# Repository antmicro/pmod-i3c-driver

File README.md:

# PMOD I3C Driver

Copyright (c) 2024 [Antmicro](https://www.antmicro.com)

## Overview

This project contains open hardware design files for a simple expansion PCB with two push-pull digital output drivers composed of discrete MOSFETs.
This allows to use the board with FPGA-driven systems to implement I3C output stage driver which can act as open drain or push-pull. 
The driver topology is switchable via digital control signals from FPGA-side.
A separate set of control signals allows to activate pull-up or pull-down resistors connected to the output signals.
The design files were prepared in KiCad 9.x.

## Key features

* Two independent digital output stages configurable as push-pull or open drain
* Switchable pull-up and pull-down resistors
* The board is compatible with PMOD (3.3V logic) expansion connector 
* The board is compatible with a 24-pin proto header (J3) available on AMD (Xilinx) [ZCU106 Evaluation Kit](https://www.xilinx.com/products/boards-and-kits/zcu106.html) 

## Project structure

The main directory contains KiCad PCB project files, a LICENSE, and a README.
The remaining files are stored in the following directories: 

* `img` - contains graphics for this README 
* `doc` - contains board schematic in PDF format

## Licensing

This project is published under the [Apache-2.0](LICENSE) license.

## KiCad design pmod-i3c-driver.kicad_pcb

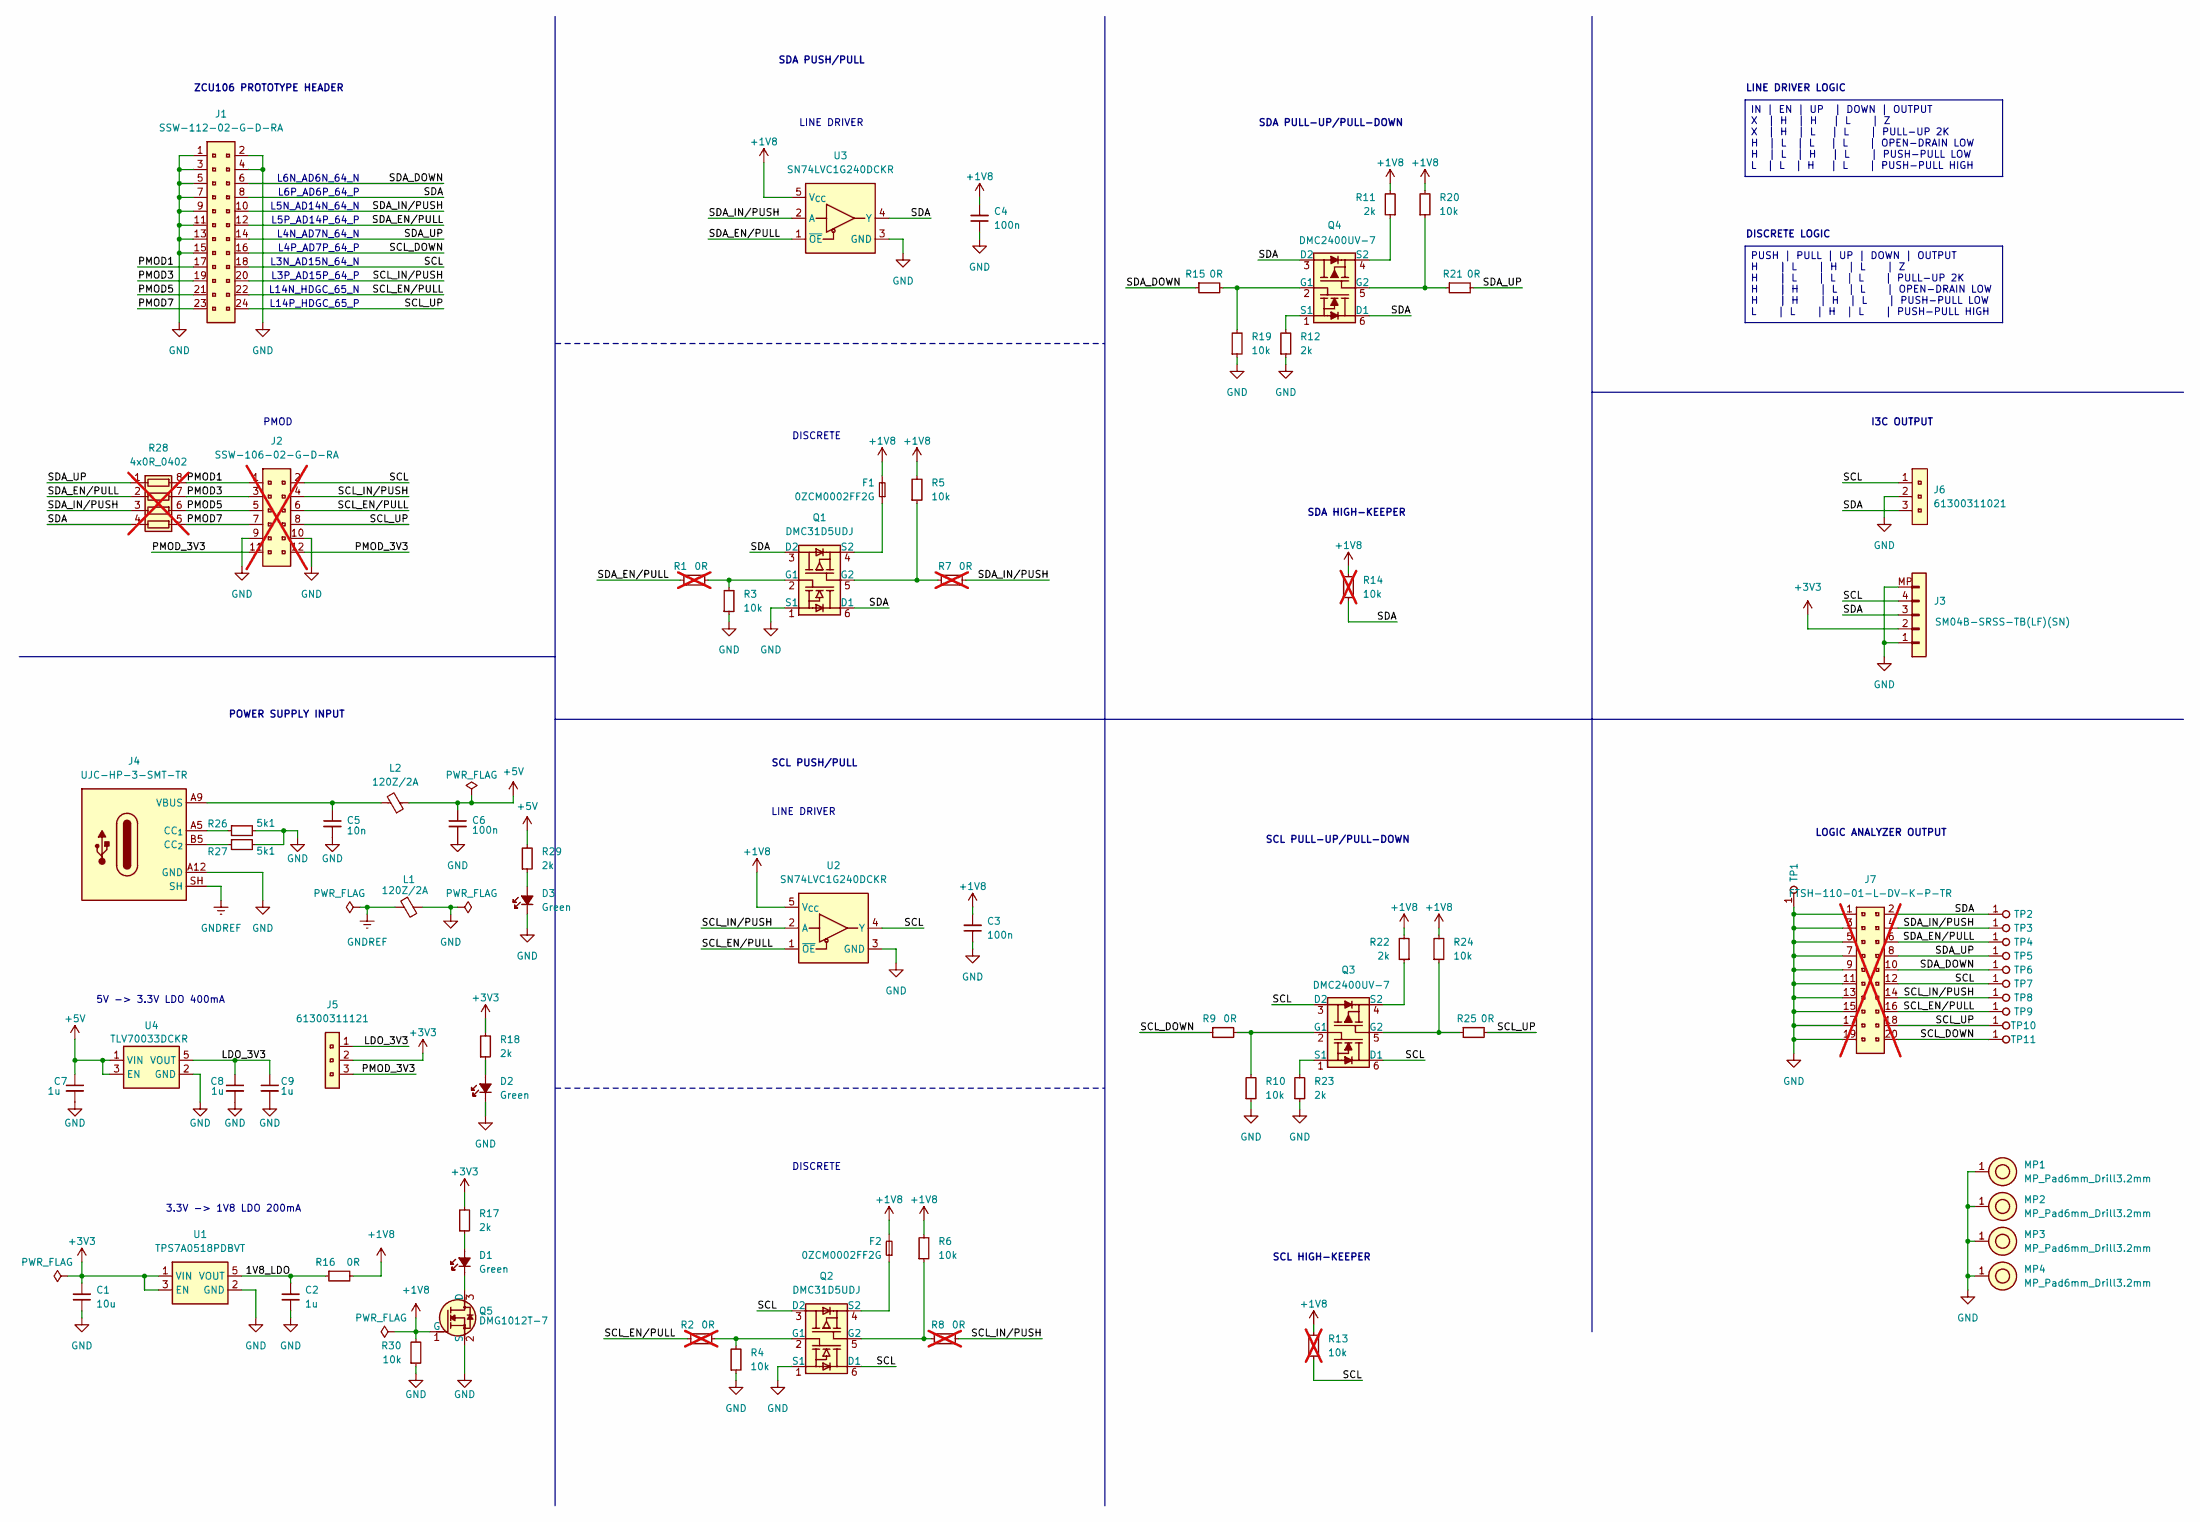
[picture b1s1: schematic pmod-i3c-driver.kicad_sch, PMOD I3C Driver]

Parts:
C1: C_10u_0402; C_0402_1005Metric; MPN CC0402MRX5R5BB106
C2: C_1u_0402; C_0402_1005Metric; MPN C1005X6S1A105K050BC
C3, C4: C_100n_0402; C_0402_1005Metric; Voltage 50V; MPN GRM155R61H104KE14D
C5: C_10n_0402; C_0402_1005Metric; Voltage 50V; MPN GRM155R71H103KA88D
C6: C_100n_16V_X7R_0402; C_0402_1005Metric; Voltage 16V; MPN C0402C104J4RAC7411
C7, C8, C9: C_1u_0603; C_0603_1608Metric; MPN 0603YD105KAT2A
D1, D2, D3: LED_G_0402_VLMTG1500-GS08; LED_0402_1005Metric_G; MPN VLMTG1500-GS08
F1, F2: F_20mA_0603; F_0603_1608Metric; MPN 0ZCM0002FF2G
J1: PinSocket_2x12_P2.54mm_Drill1.04mm_Horizontal; MPN SSW-112-02-G-D-RA
J2: PinSocket_2x6_P2.54mm_Drill1.04mm_Horizontal; MPN SSW-106-02-G-D-RA; not fitted
J3: JST_SH_1x4_SM04B-SRSS-TB-LF-SN; Conn_JST_SH_1x4_SM04B-SRSS-TB-LF-SN; MPN SM04B-SRSS-TB(LF)(SN)
J4: USB-C_CUI_UJC-HP-3-SMT-TR; USB-C_Receptacle_CUI_UJC-HP-3-SMT-TR; MPN UJC-HP-3-SMT-TR
J5: PinHeader_1x3_P2.54mm_Drill1.1mm; MPN 61300311121
J6: PinHeader_1x3_P2.54mm_Drill1.1mm_Horizontal; PinHeader_1x3_P2.54mm_Horizontal; MPN 61300311021
J7: PinHeader_2x10_P1.27mm_SMD_Latch; MPN FTSH-110-01-L-DV-K-P-TR; not fitted
L1, L2: FB_120Z_2A_Murata-BLM18PG_0603; FB_0603_1608Metric; MPN BLM18PG121SN1D
MP1, MP2, MP3, MP4: MP_Pad6mm_Drill3.2mm
Q1, Q2: DMC31D5UDJ; SOT-963; MPN DMC31D5UDJ
Q3, Q4: DMC2400UV-7; SOT-563; MPN DMC2400UV-7
Q5: DMG1012T-7; SOT-523; MPN DMG1012T-7
R1, R2, R7, R8: R_0R_0402; R_0402_1005Metric; MPN ERJ2GE0R00X; not fitted
R3, R4, R5, R6, R10, R19, R20, R24, R30: R_10k_0402; R_0402_1005Metric; Tolerance 1%; MPN CR0402-FX-1002GLF
R9, R15, R16, R21, R25: R_0R_0402; R_0402_1005Metric; MPN ERJ2GE0R00X
R11, R12, R17, R18, R22, R23, R29: R_2k_0402; R_0402_1005Metric; Tolerance 1%; MPN CR0402-FX-2001GLF
R13, R14: R_10k_0402; R_0402_1005Metric; Tolerance 1%; MPN CR0402-FX-1002GLF; not fitted
R26, R27: R_5k1_0402; R_0402_1005Metric; Tolerance 1%; MPN CR0402-FX-5101GLF
R28: 4x0R_0402_array; 4x0R_0402_array_EXB28V; MPN EXB28VR000X; not fitted
TP1, TP2, TP3, TP4, TP5, TP6, TP7, TP8, TP9, TP10, TP11: TP_1.5mm_SMD; TP_SMD_1.5mm
U1: TPS7A0518P_SOT23-5; SOT-23-5; MPN TPS7A0518PDBVT
U2, U3: SN74LVC1G240_SC70; SOT-353; MPN SN74LVC1G240DCKR
U4: TLV70033_SC70; SC-70-5; MPN TLV70033DCKR

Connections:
+1V8: C3.2, C4.2, F1.2, F2.2, Q5.1 (G), R5.2, R6.2, R11.2, R13.2, R14.2, R16.2, R20.2, R22.2, R24.2, R30.2, U2.5 (V_{CC}), U3.5 (V_{CC})
+3V3: C1.2, J3.2, J5.2, R17.2, R18.2, U1.1 (VIN), U1.3 (EN)
+5V: C6.1, C7.1, L2.1, R29.2, U4.1 (VIN), U4.3 (EN)
/1V8_LDO: C2.2, R16.1, U1.5 (VOUT)
/LDO_3V3: C8.1, C9.1, J5.1, U4.5 (VOUT)
/PMOD1: J1.17, J2.1, R28.8 (R1.2)
/PMOD3: J1.19, J2.3, R28.7 (R2.2)
/PMOD5: J1.21, J2.5, R28.6 (R3.2)
/PMOD7: J1.23, J2.7, R28.5 (R4.2)
/PMOD_3V3: J2.11, J2.12, J5.3
/SCL: J1.18, J2.2, J3.4, J6.1, J7.12, Q2.3 (D2), Q2.6 (D1), Q3.3 (D2), Q3.6 (D1), R13.1, TP7.1, U2.4 (Y)
/SCL_DOWN: J1.16, J7.20, R9.1, TP11.1
/SCL_EN/PULL: J1.22, J2.6, J7.16, R2.1, TP9.1, U2.1 (~OE)
/SCL_IN/PUSH: J1.20, J2.4, J7.14, R8.2, TP8.1, U2.2 (A)
/SCL_UP: J1.24, J2.8, J7.18, R25.2, TP10.1
/SDA: J1.8, J3.3, J6.3, J7.2, Q1.3 (D2), Q1.6 (D1), Q4.3 (D2), Q4.6 (D1), R14.1, R28.4 (R4.1), TP2.1, U3.4 (Y)
/SDA_DOWN: J1.6, J7.10, R15.1, TP6.1
/SDA_EN/PULL: J1.12, J7.6, R1.1, R28.2 (R2.1), TP4.1, U3.1 (~OE)
/SDA_IN/PUSH: J1.10, J7.4, R7.2, R28.3 (R3.1), TP3.1, U3.2 (A)
/SDA_UP: J1.14, J7.8, R21.2, R28.1 (R1.1), TP5.1
GND: C1.1, C2.1, C3.1, C4.1, C5.2, C6.2, C7.2, C8.2, C9.2, D2.1 (C), D3.1 (C), J1.1, J1.2, J1.3, J1.4, J1.5, J1.7, J1.9, J1.11, J1.13, J1.15, J2.9, J2.10, J3.1, J3.MP, J4.A12 (GND), J4.B12 (GND), J6.2, J7.1, J7.3, J7.5, J7.7, J7.9, J7.11, J7.13, J7.15, J7.17, J7.19, L1.2, MP1.1, MP2.1, MP3.1, MP4.1, Q1.1 (S1), Q2.1 (S1), Q5.2 (S), R3.1, R4.1, R10.1, R12.1, R19.1, R23.1, R26.2, R27.2, R30.1, TP1.1, U1.2 (GND), U2.3 (GND), U3.3 (GND), U4.2 (GND)
GNDREF: J4.SH, L1.1
unnamed: C5.1, J4.A9 (VBUS), J4.B9 (VBUS), L2.2
unnamed: D1.2 (A), R17.1
unnamed: D1.1 (C), Q5.3 (D)
unnamed: D2.2 (A), R18.1
unnamed: D3.2 (A), R29.1
unnamed: J4.A5 (CC_{1}), R26.1
unnamed: J4.B5 (CC_{2}), R27.1
unnamed: Q1.2 (G1), R1.2, R3.2
unnamed: Q1.5 (G2), R5.1, R7.1
unnamed: F1.1, Q1.4 (S2)
unnamed: Q2.2 (G1), R2.2, R4.2
unnamed: Q2.5 (G2), R6.1, R8.1
unnamed: F2.1, Q2.4 (S2)
unnamed: Q3.2 (G1), R9.2, R10.2
unnamed: Q3.5 (G2), R24.1, R25.1
unnamed: Q3.1 (S1), R23.2
unnamed: Q3.4 (S2), R22.1
unnamed: Q4.2 (G1), R15.2, R19.2
unnamed: Q4.5 (G2), R20.1, R21.1
unnamed: Q4.1 (S1), R12.2
unnamed: Q4.4 (S2), R11.1

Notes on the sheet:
LINE DRIVER
L4N_AD7N_64_N
DISCRETE
L3N_AD15N_64_N
DISCRETE LOGIC
LINE DRIVER LOGIC
L6P_AD6P_64_P
SCL PUSH/PULL
L14N_HDGC_65_N
SDA PUSH/PULL
5V -> 3.3V LDO 400mA
LOGIC ANALYZER OUTPUT
L6N_AD6N_64_N
L5N_AD14N_64_N
SDA HIGH-KEEPER
L4P_AD7P_64_P
L5P_AD14P_64_P
PMOD
SCL PULL-UP/PULL-DOWN
ZCU106 PROTOTYPE HEADER
SCL HIGH-KEEPER
I3C OUTPUT
L3P_AD15P_64_P
L14P_HDGC_65_P
SDA PULL-UP/PULL-DOWN
POWER SUPPLY INPUT
3.3V -> 1V8 LDO 200mA
IN | EN | UP | DOWN | OUTPUT X | H | H | L | Z X | H | L | L | PULL-UP 2K H | L | L | L | OPEN-DRAIN LOW H | L | H | L | PUSH-PULL LOW L | L | H | L | PUSH-PULL HIGH
PUSH | PULL | UP | DOWN | OUTPUT H | L | H | L | Z H | L | L | L | PULL-UP 2K H | H | L | L | OPEN-DRAIN LOW H | H | H | L | PUSH-PULL LOW L | L | H | L | PUSH-PULL HIGH

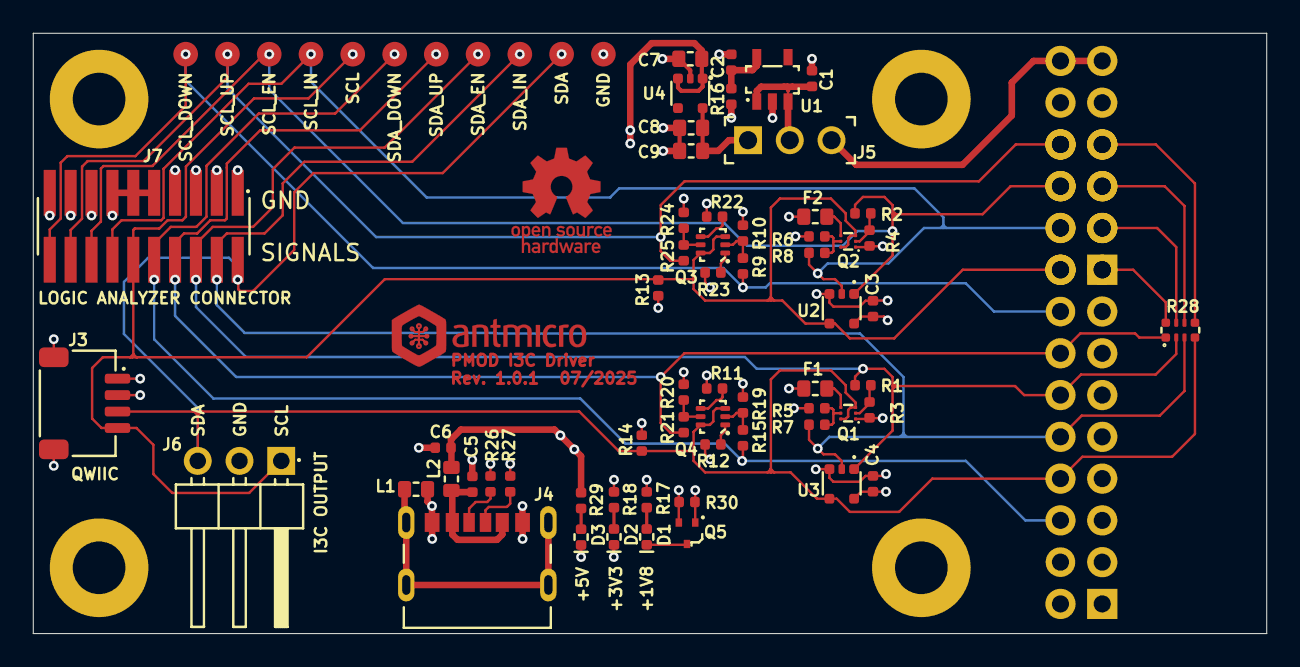
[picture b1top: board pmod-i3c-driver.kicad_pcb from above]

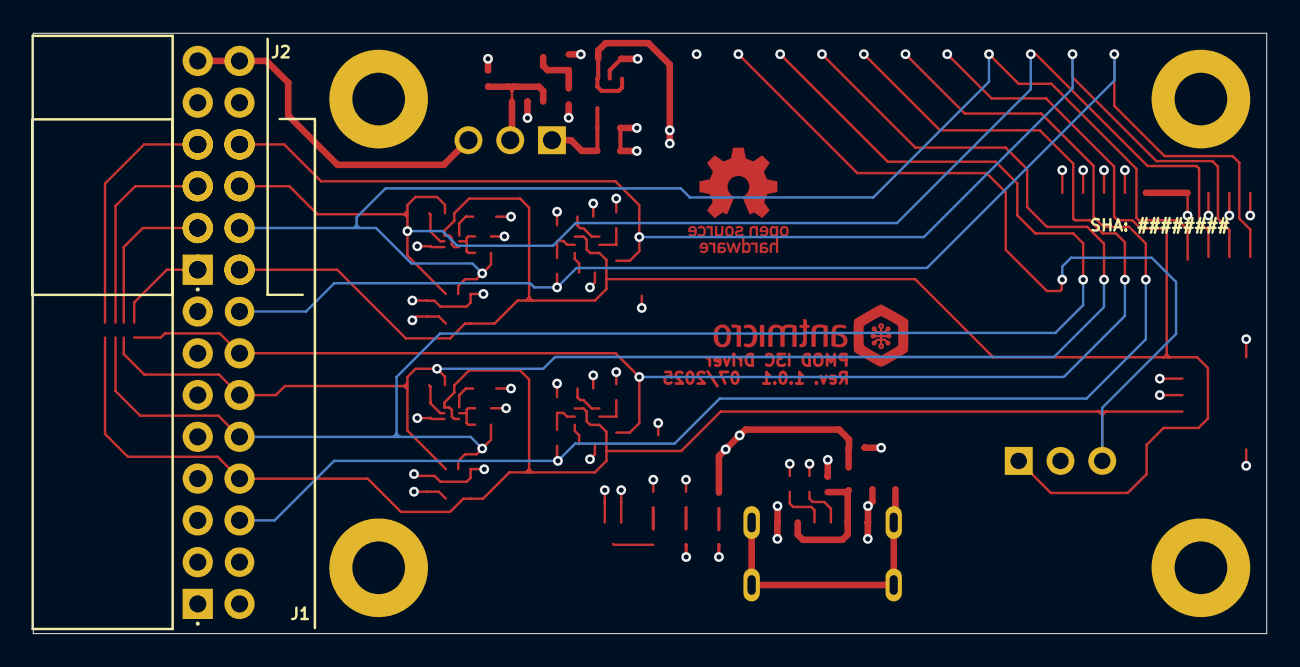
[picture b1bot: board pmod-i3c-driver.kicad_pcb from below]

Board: 4 copper layers, 75.0 x 36.5 mm, 77 parts (2 on the bottom side), 43 nets.

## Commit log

2024-11-11 [#68164] Add automation script
2024-11-11 [#68164] Update PMOS connections on PCB
2024-11-11 [#68164] Update power supply, input and output connectors
2024-11-11 Add simple README
2024-11-11 [#68164] Add schematic and PCB
2024-11-11 [#68164] Update PMOS connections on schematic
2024-11-11 [#68164] Update components, rotate PCB
2024-11-11 Cleanup
2024-11-11 [#68164] Add logos, align mounting holes
2024-11-11 [#68164] Add gitignore
2024-11-11 [#68164] Update schematic
2024-11-11 [#68164] Clean ERC
2024-11-11 [#68164] Populate resistors
2024-11-11 [#68164] Apply changes to PCB
2024-11-11 [#68164] Clean DRC
2024-11-11 Update naming convention
2024-11-11 Make J7 DNP
2024-11-11 README updates
2024-11-11 README: Add 3D render
2024-11-12 Add PDF schematic
2024-11-19 Use monospace font for schematic
2025-07-21 [#80692] Bump CI template
2025-07-21 [#80692] Bump design to KiCad 9.0
2025-07-22 [#80692] Fix DNP
2025-07-22 [#80692] Update symbols, fix ERC
2025-07-22 [#80692] Update footprints, clean ERC, bump rev to 1.0.1
2025-07-23 [#80692] README: Update KiCad version
2025-07-25 [#80692] Update silkscreen and DNP

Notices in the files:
parts and their libraries:
License: Apache-2.0
